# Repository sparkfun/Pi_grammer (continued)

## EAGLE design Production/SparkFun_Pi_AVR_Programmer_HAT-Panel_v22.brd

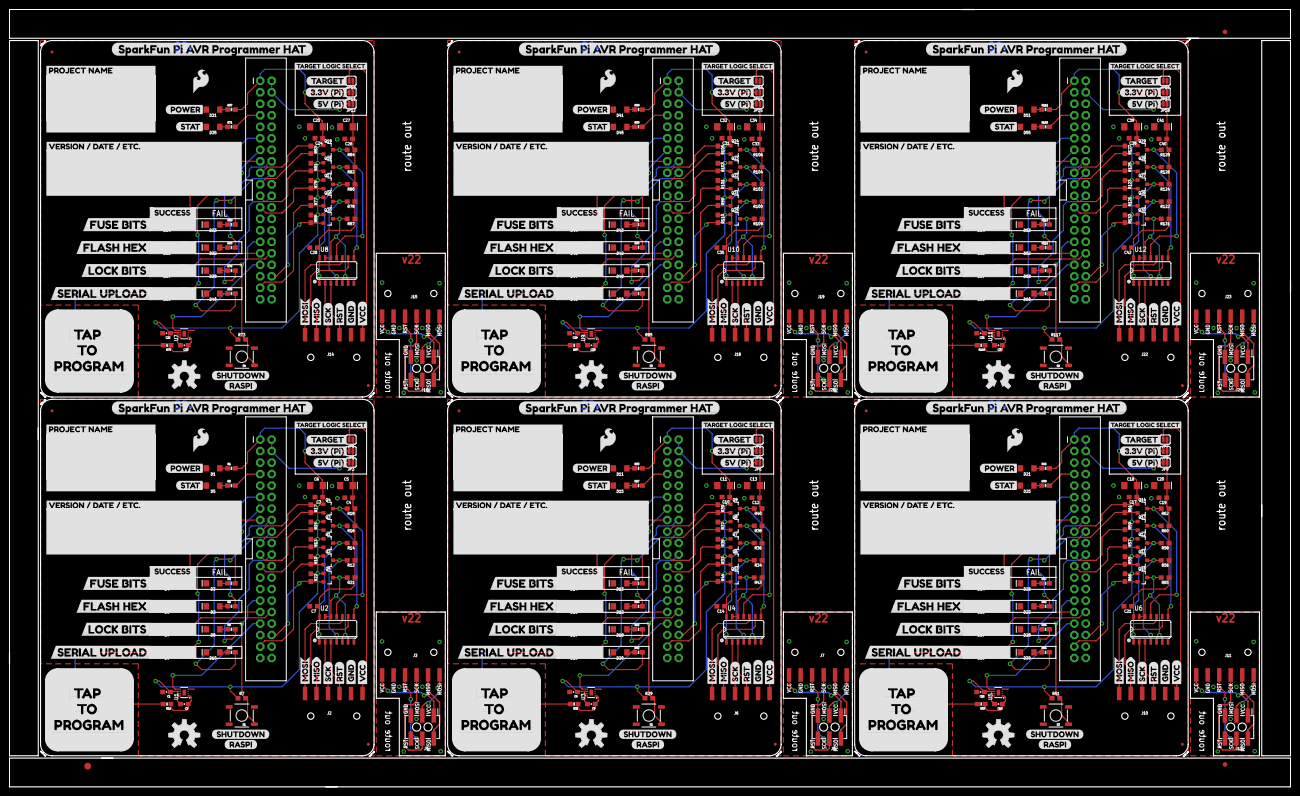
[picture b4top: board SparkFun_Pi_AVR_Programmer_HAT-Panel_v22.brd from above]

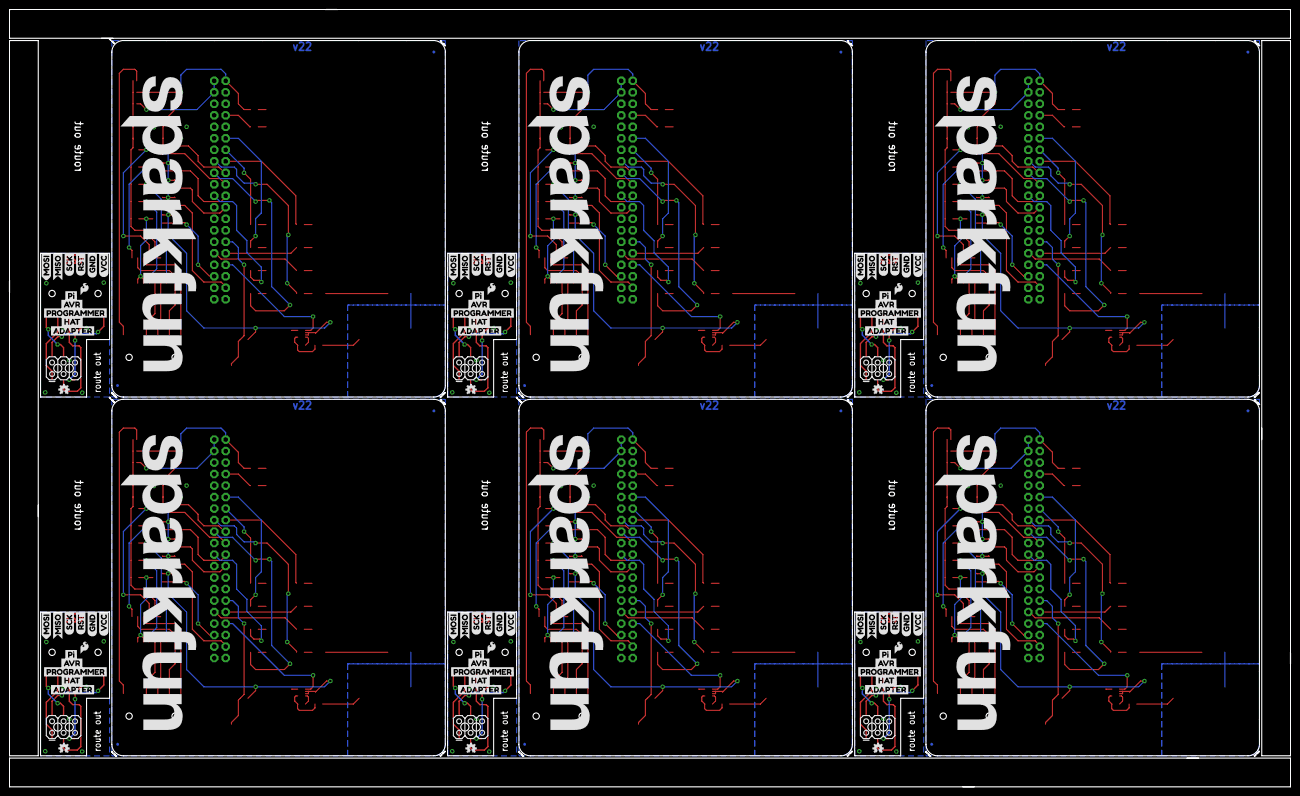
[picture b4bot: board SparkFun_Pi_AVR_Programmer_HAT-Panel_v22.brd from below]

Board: 2 copper layers, 283.0 x 171.7 mm, 597 parts (96 on the bottom side), 288 nets.

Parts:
C1, C8, C15, C22, C29, C36: 0.1uF; 0603-CAP
C2, C9, C16, C23, C30, C37: 10nF; 0603-CAP
C3, C4, C7, C10, C12, C14, C17, C19, C21, C24, C26, C28, C31, C33, C35, C38, C40, C42: 0.1uF; 0603
C5, C6, C11, C13, C18, C20, C25, C27, C32, C34, C39, C41: 10uF; EIA3216
D1, D4, D5, D6, D7, D9, D11, D14, D15, D16, D17, D19, D21, D24, D25, D26, D27, D29, D31, D34, D35, D36, D37, D39, D41, D44, D45, D46, D47, D49, D51, D54, D55, D56, D57, D59: GREEN; LED-1206
D2, D3, D8, D10, D12, D13, D18, D20, D22, D23, D28, D30, D32, D33, D38, D40, D42, D43, D48, D50, D52, D53, D58, D60: RED; LED-1206
E$1: FIDUCIAL-1.5X3
E$5, E$6: FIDUCIAL-1X2
FD1, FD2, FD3, FD4, FD5, FD6, FD7, FD8, FD9, FD10, FD11, FD12, FD13, FD14, FD15, FD16, FD17, FD18, FD19, FD20, FD21, FD22, FD23, FD24: FIDUCIALUFIDUCIAL; FIDUCIAL-MICRO
J1, J5, J9, J13, J17, J21: RASPBERRYPI-B+-GPIO; 2X20-SHROUDED
J2, J6, J10, J14, J18, J22: SPI; 1X06-SMD_RA_MALE
J3, J7, J11, J15, J19, J23: CABLE; 1X06-SMD_RA_MALE
J4, J8, J12, J16, J20, J24: AVR 3X2 TARGET; 2X3_SMT_POSTS
JP1, JP3, JP4, JP6, JP8, JP9, JP11, JP12, JP14, JP15, JP17, JP18: SMT-JUMPER_2_NO_SILK
JP2, JP5, JP7, JP10, JP13, JP16: SMT-JUMPER_2_NC_PASTE_SILK
LOGO1, LOGO7, LOGO12, LOGO17, LOGO22, LOGO27: SFE_LOGO_FLAME.2_INCH; SFE_LOGO_FLAME_.2
LOGO2, LOGO6, LOGO11, LOGO16, LOGO21, LOGO26: OSHW-LOGOL; OSHW-LOGO-L
LOGO3, LOGO8, LOGO13, LOGO18, LOGO23, LOGO28: SFE_LOGO_NAME.6_INCH; SFE_LOGO_NAME_.6
LOGO4, LOGO9, LOGO14, LOGO19, LOGO24, LOGO29: SFE_LOGO_FLAME.1_INCH; SFE_LOGO_FLAME_.1
LOGO5, LOGO10, LOGO15, LOGO20, LOGO25, LOGO30: OSHW-LOGOMINI; OSHW-LOGO-MINI
Q1, Q2, Q3, Q4, Q5, Q6, Q7, Q8, Q9, Q10, Q11, Q12, Q13, Q14, Q15, Q16, Q17, Q18, Q19, Q20, Q21, Q22, Q23, Q24, Q25, Q26, Q27, Q28, Q29, Q30: 220mA/50V/3.5Ω; SOT23-3
R1, R2, R3, R4, R5, R6, R8, R9, R19, R20, R23, R24, R25, R26, R27, R28, R30, R32, R41, R42, R45, R46, R47, R48, R49, R50, R52, R54, R63, R64, R67, R68, R69, R70, R71, R72, R74, R76, R85, R86, R89, R90, R91, R92, R93, R94, R96, R98, R107, R108, R111, R112, R113, R114, R115, R116, R118, R120, R129, R130: 1K; 0603-RES
R7, R29, R51, R73, R95, R117: 1k; 0603
R10, R12, R13, R14, R15, R16, R17, R18, R21, R22, R33, R34, R35, R36, R37, R38, R39, R40, R43, R44, R55, R56, R57, R58, R59, R60, R61, R62, R65, R66, R77, R78, R79, R80, R81, R82, R83, R84, R87, R88, R99, R100, R101, R102, R103, R104, R105, R106, R109, R110, R121, R122, R123, R124, R125, R126, R127, R128, R131, R132: 10k; 0603
R11, R31, R53, R75, R97, R119: 10k; 0603-RES
S1, S2, S3, S4, S5, S6: TACTILE-SWITCH-SMD
U1, U3, U5, U7, U9, U11: AT42QT1010 - UDFN; UDFN/USON_8_PAD
U2, U4, U6, U8, U10, U12: 74LVC4066; SO14
U$1, U$37, U$73, U$109, U$145, U$181: SPARKFUN_PI_AVR_PROGRAMMER_HAT0
U$2, U$38, U$74, U$110, U$146, U$182: PROJECT_NAME0
U$3, U$39, U$75, U$111, U$147, U$183: VERSION_#_DATE_#_ETC#0
U$4, U$40, U$76, U$112, U$148, U$184: TARGET_LOGIC_SELECT4
U$5, U$41, U$77, U$113, U$149, U$185: POWER0
U$6, U$42, U$78, U$114, U$150, U$186: STAT1
U$7, U$43, U$79, U$115, U$151, U$187: SHUTDOWN2
U$8, U$44, U$80, U$116, U$152, U$188: RASPI3
U$9, U$45, U$81, U$117, U$153, U$189: 3#3V_#PI#7
U$10, U$46, U$82, U$118, U$154, U$190: 5V_#PI#8
U$11, U$47, U$83, U$119, U$155, U$191: TARGET0
U$12, U$48, U$84, U$120, U$156, U$192: MISO1
U$13, U$49, U$85, U$121, U$157, U$193: MOSI0
U$14, U$50, U$86, U$122, U$158, U$194: SCK2
U$15, U$51, U$87, U$123, U$159, U$195: RST3
U$16, U$52, U$88, U$124, U$160, U$196: GND4
U$17, U$62, U$98, U$134, U$170, U$206: GND1
U$18, U$53, U$89, U$125, U$161, U$197: TAP0
U$19, U$54, U$90, U$126, U$162, U$198: TO1
U$20, U$55, U$91, U$127, U$163, U$199: PROGRAM2
U$21, U$31, U$61, U$67, U$97, U$103, U$133, U$139, U$169, U$175, U$205, U$211: VCC0
U$22, U$56, U$92, U$128, U$164, U$200: SUCCESS0
U$23, U$57, U$93, U$129, U$165, U$201: FUSE_BITS2
U$24, U$58, U$94, U$130, U$166, U$202: FLASH_HEX3
U$25, U$59, U$95, U$131, U$167, U$203: LOCK_BITS4
U$26, U$60, U$96, U$132, U$168, U$204: SERIAL_UPLOAD5
U$27, U$63, U$99, U$135, U$171, U$207: MISO5
U$28, U$64, U$100, U$136, U$172, U$208: MOSI4
U$29, U$65, U$101, U$137, U$173, U$209: RST2
U$30, U$66, U$102, U$138, U$174, U$210: SCK3
U$32, U$68, U$104, U$140, U$176, U$212: PI0
U$33, U$69, U$105, U$141, U$177, U$213: AVR1
U$34, U$70, U$106, U$142, U$178, U$214: PROGRAMMER2
U$35, U$71, U$107, U$143, U$179, U$215: HAT3
U$36, U$72, U$108, U$144, U$180, U$216: ADAPTER4

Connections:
3.3V: C1.1, C3.1, C6.+, J1.1, J1.17, JP1.2, Q1.1, Q2.1, Q3.1, Q4.1, Q5.1, R1.2, R7.1, R10.1, R13.1, R15.1, R17.1, R22.1, U1.6, U1.7
3.3V1: C8.1, C10.1, C11.+, J5.1, J5.17, JP4.2, Q6.1, Q7.1, Q8.1, Q9.1, Q10.1, R23.2, R29.1, R33.1, R35.1, R37.1, R39.1, R44.1, U3.6, U3.7
3.3V2: C15.1, C17.1, C18.+, J9.1, J9.17, JP8.2, Q11.1, Q12.1, Q13.1, Q14.1, Q15.1, R45.2, R51.1, R55.1, R57.1, R59.1, R61.1, R66.1, U5.6, U5.7
3.3V3: C22.1, C24.1, C25.+, J13.1, J13.17, JP11.2, Q16.1, Q17.1, Q18.1, Q19.1, Q20.1, R67.2, R73.1, R77.1, R79.1, R81.1, R83.1, R88.1, U7.6, U7.7
3.3V4: C29.1, C31.1, C32.+, J17.1, J17.17, JP14.2, Q21.1, Q22.1, Q23.1, Q24.1, Q25.1, R89.2, R95.1, R99.1, R101.1, R103.1, R105.1, R110.1, U9.6, U9.7
3.3V5: C36.1, C38.1, C39.+, J21.1, J21.17, JP17.2, Q26.1, Q27.1, Q28.1, Q29.1, Q30.1, R111.2, R117.1, R121.1, R123.1, R125.1, R127.1, R132.1, U11.6, U11.7
5V: J1.2, J1.4, JP3.2
5V1: J5.2, J5.4, JP6.2
5V2: J9.2, J9.4, JP9.2
5V3: J13.2, J13.4, JP12.2
5V4: J17.2, J17.4, JP15.2
5V5: J21.2, J21.4, JP18.2
BRD_MISO: J2.2, U2.9
BRD_MISO1: J6.2, U4.9
BRD_MISO2: J10.2, U6.9
BRD_MISO3: J14.2, U8.9
BRD_MISO4: J18.2, U10.9
BRD_MISO5: J22.2, U12.9
BRD_MOSI: J2.1, U2.10
BRD_MOSI1: J6.1, U4.10
BRD_MOSI2: J10.1, U6.10
BRD_MOSI3: J14.1, U8.10
BRD_MOSI4: J18.1, U10.10
BRD_MOSI5: J22.1, U12.10
BRD_RST: J2.4, U2.3
BRD_RST1: J6.4, U4.3
BRD_RST2: J10.4, U6.3
BRD_RST3: J14.4, U8.3
BRD_RST4: J18.4, U10.3
BRD_RST5: J22.4, U12.3
BRD_SCK: J2.3, U2.2
BRD_SCK1: J6.3, U4.2
BRD_SCK2: J10.3, U6.2
BRD_SCK3: J14.3, U8.2
BRD_SCK4: J18.3, U10.2
BRD_SCK5: J22.3, U12.2
CAPSENSE: J1.33, U1.5
CAPSENSE1: J5.33, U3.5
CAPSENSE2: J9.33, U5.5
CAPSENSE3: J13.33, U7.5
CAPSENSE4: J17.33, U9.5
CAPSENSE5: J21.33, U11.5
FLASH_HEX_FAIL: J1.11, R2.2
FLASH_HEX_FAIL1: J5.11, R24.2
FLASH_HEX_FAIL2: J9.11, R46.2
FLASH_HEX_FAIL3: J13.11, R68.2
FLASH_HEX_FAIL4: J17.11, R90.2
FLASH_HEX_FAIL5: J21.11, R112.2
FLASH_HEX_PASS: J1.31, R6.2
FLASH_HEX_PASS1: J5.31, R28.2
FLASH_HEX_PASS2: J9.31, R50.2
FLASH_HEX_PASS3: J13.31, R72.2
FLASH_HEX_PASS4: J17.31, R94.2
FLASH_HEX_PASS5: J21.31, R116.2
FUSE_BITS_FAIL: J1.13, R3.2
FUSE_BITS_FAIL1: J5.13, R25.2
FUSE_BITS_FAIL2: J9.13, R47.2
FUSE_BITS_FAIL3: J13.13, R69.2
FUSE_BITS_FAIL4: J17.13, R91.2
FUSE_BITS_FAIL5: J21.13, R113.2
FUSE_BITS_PASS: J1.15, R4.2
FUSE_BITS_PASS1: J5.15, R26.2
FUSE_BITS_PASS2: J9.15, R48.2
FUSE_BITS_PASS3: J13.15, R70.2
FUSE_BITS_PASS4: J17.15, R92.2
FUSE_BITS_PASS5: J21.15, R114.2
GND: C1.2, C3.2, C4.2, C5.-, C6.-, C7.2, D1.C, D2.C, D3.C, D4.C, D5.C, D6.C, D7.C, D8.C, D9.C, D10.C, J1.6, J1.9, J1.14, J1.20, J1.25, J1.30, J1.34, J1.39, J2.5, S1.3, U1.4, U2.7
GND1: C8.2, C10.2, C11.-, C12.2, C13.-, C14.2, D11.C, D12.C, D13.C, D14.C, D15.C, D16.C, D17.C, D18.C, D19.C, D20.C, J5.6, J5.9, J5.14, J5.20, J5.25, J5.30, J5.34, J5.39, J6.5, S2.3, U3.4, U4.7
GND2: C15.2, C17.2, C18.-, C19.2, C20.-, C21.2, D21.C, D22.C, D23.C, D24.C, D25.C, D26.C, D27.C, D28.C, D29.C, D30.C, J9.6, J9.9, J9.14, J9.20, J9.25, J9.30, J9.34, J9.39, J10.5, S3.3, U5.4, U6.7
GND3: C22.2, C24.2, C25.-, C26.2, C27.-, C28.2, D31.C, D32.C, D33.C, D34.C, D35.C, D36.C, D37.C, D38.C, D39.C, D40.C, J13.6, J13.9, J13.14, J13.20, J13.25, J13.30, J13.34, J13.39, J14.5, S4.3, U7.4, U8.7
GND4: C29.2, C31.2, C32.-, C33.2, C34.-, C35.2, D41.C, D42.C, D43.C, D44.C, D45.C, D46.C, D47.C, D48.C, D49.C, D50.C, J17.6, J17.9, J17.14, J17.20, J17.25, J17.30, J17.34, J17.39, J18.5, S5.3, U9.4, U10.7
GND5: C36.2, C38.2, C39.-, C40.2, C41.-, C42.2, D51.C, D52.C, D53.C, D54.C, D55.C, D56.C, D57.C, D58.C, D59.C, D60.C, J21.6, J21.9, J21.14, J21.20, J21.25, J21.30, J21.34, J21.39, J22.5, S6.3, U11.4, U12.7
GND_C: J3.5, J4.5
GND_C1: J7.5, J8.5
GND_C2: J11.5, J12.5
GND_C3: J15.5, J16.5
GND_C4: J19.5, J20.5
GND_C5: J23.5, J24.5
LOCK_BITS_FAIL: J1.22, R9.2
LOCK_BITS_FAIL1: J5.22, R32.2
LOCK_BITS_FAIL2: J9.22, R54.2
LOCK_BITS_FAIL3: J13.22, R76.2
LOCK_BITS_FAIL4: J17.22, R98.2
LOCK_BITS_FAIL5: J21.22, R120.2
LOCK_BITS_PASS: J1.32, R8.2
LOCK_BITS_PASS1: J5.32, R30.2
LOCK_BITS_PASS2: J9.32, R52.2
LOCK_BITS_PASS3: J13.32, R74.2
LOCK_BITS_PASS4: J17.32, R96.2
LOCK_BITS_PASS5: J21.32, R118.2
MISO: J1.21, Q3.2, R15.2
MISO1: J5.21, Q8.2, R37.2
MISO2: J9.21, Q13.2, R59.2
MISO3: J13.21, Q18.2, R81.2
MISO4: J17.21, Q23.2, R103.2
MISO5: J21.21, Q28.2, R125.2
MISO_C: J3.2, J4.2
MISO_C1: J7.2, J8.2
MISO_C2: J11.2, J12.2
MISO_C3: J15.2, J16.2
MISO_C4: J19.2, J20.2
MISO_C5: J23.2, J24.2
MISO_T: Q3.3, R16.2, U2.8
MISO_T1: Q8.3, R38.2, U4.8
MISO_T2: Q13.3, R60.2, U6.8
MISO_T3: Q18.3, R82.2, U8.8
MISO_T4: Q23.3, R104.2, U10.8
MISO_T5: Q28.3, R126.2, U12.8
MOSI: J1.19, Q4.2, R17.2
MOSI1: J5.19, Q9.2, R39.2
MOSI2: J9.19, Q14.2, R61.2
MOSI3: J13.19, Q19.2, R83.2
MOSI4: J17.19, Q24.2, R105.2
MOSI5: J21.19, Q29.2, R127.2
MOSI_C: J3.1, J4.3
MOSI_C1: J7.1, J8.3
MOSI_C2: J11.1, J12.3
MOSI_C3: J15.1, J16.3
MOSI_C4: J19.1, J20.3
MOSI_C5: J23.1, J24.3
MOSI_T: Q4.3, R18.2, U2.11
MOSI_T1: Q9.3, R40.2, U4.11
MOSI_T2: Q14.3, R62.2, U6.11
MOSI_T3: Q19.3, R84.2, U8.11
MOSI_T4: Q24.3, R106.2, U10.11
MOSI_T5: Q29.3, R128.2, U12.11
unnamed: D6.A, R6.1
unnamed: D1.A, R1.1
unnamed: D2.A, R2.1
unnamed: D3.A, R3.1
unnamed: D7.A, R8.1
unnamed: D4.A, R4.1
unnamed: D5.A, R5.1
unnamed: D8.A, R9.1
unnamed: D11.A, R23.1
unnamed: C2.2, U1.8
unnamed: C2.1, R11.1, U1.1
unnamed: D12.A, R24.1
unnamed: D9.A, R19.1
unnamed: D10.A, R20.1
unnamed: D13.A, R25.1
unnamed: D14.A, R26.1
unnamed: D15.A, R27.1
unnamed: D16.A, R28.1
unnamed: D17.A, R30.1
unnamed: C9.2, U3.8
unnamed: C9.1, R31.1, U3.1
unnamed: D18.A, R32.1
unnamed: D19.A, R41.1
unnamed: D20.A, R42.1
unnamed: D21.A, R45.1
unnamed: D22.A, R46.1
unnamed: D23.A, R47.1
unnamed: D24.A, R48.1
unnamed: D25.A, R49.1
unnamed: D26.A, R50.1
unnamed: D27.A, R52.1
unnamed: C16.2, U5.8
unnamed: C16.1, R53.1, U5.1
unnamed: D28.A, R54.1
unnamed: D29.A, R63.1
unnamed: D30.A, R64.1
unnamed: D31.A, R67.1
unnamed: D32.A, R68.1
unnamed: D33.A, R69.1
unnamed: D34.A, R70.1
unnamed: D35.A, R71.1
unnamed: D36.A, R72.1
unnamed: D37.A, R74.1
unnamed: C23.2, U7.8
unnamed: C23.1, R75.1, U7.1
unnamed: D38.A, R76.1
unnamed: D39.A, R85.1
unnamed: D40.A, R86.1
unnamed: D41.A, R89.1
unnamed: D42.A, R90.1
unnamed: D43.A, R91.1
unnamed: D44.A, R92.1
unnamed: D45.A, R93.1
unnamed: D46.A, R94.1
unnamed: D47.A, R96.1
unnamed: C30.2, U9.8
unnamed: C30.1, R97.1, U9.1
unnamed: D48.A, R98.1
unnamed: D49.A, R107.1
unnamed: D50.A, R108.1
unnamed: D51.A, R111.1
unnamed: D52.A, R112.1
unnamed: D53.A, R113.1
unnamed: D54.A, R114.1
unnamed: D55.A, R115.1
unnamed: D56.A, R116.1
unnamed: D57.A, R118.1
unnamed: C37.2, U11.8
unnamed: C37.1, R119.1, U11.1
unnamed: D58.A, R120.1
unnamed: D59.A, R129.1
unnamed: D60.A, R130.1
PGM_CTRL: J1.36, Q5.2, R22.2
PGM_CTRL1: J5.36, Q10.2, R44.2
PGM_CTRL2: J9.36, Q15.2, R66.2
PGM_CTRL3: J13.36, Q20.2, R88.2
PGM_CTRL4: J17.36, Q25.2, R110.2
PGM_CTRL5: J21.36, Q30.2, R132.2
PGM_CTRL_T: Q5.3, R21.2, U2.5, U2.6, U2.12, U2.13
PGM_CTRL_T1: Q10.3, R43.2, U4.5, U4.6, U4.12, U4.13
PGM_CTRL_T2: Q15.3, R65.2, U6.5, U6.6, U6.12, U6.13
PGM_CTRL_T3: Q20.3, R87.2, U8.5, U8.6, U8.12, U8.13
PGM_CTRL_T4: Q25.3, R109.2, U10.5, U10.6, U10.12, U10.13
PGM_CTRL_T5: Q30.3, R131.2, U12.5, U12.6, U12.12, U12.13
RST: J1.37, Q2.2, R10.2
RST1: J5.37, Q6.2, R33.2
RST2: J9.37, Q11.2, R55.2
RST3: J13.37, Q16.2, R77.2
RST4: J17.37, Q21.2, R99.2
RST5: J21.37, Q26.2, R121.2
RST_C: J3.4, J4.6
RST_C1: J7.4, J8.6
RST_C2: J11.4, J12.6
RST_C3: J15.4, J16.6
RST_C4: J19.4, J20.6
RST_C5: J23.4, J24.6
RST_T: Q2.3, R12.2, U2.4
RST_T1: Q6.3, R34.2, U4.4
RST_T2: Q11.3, R56.2, U6.4
RST_T3: Q16.3, R78.2, U8.4
RST_T4: Q21.3, R100.2, U10.4
RST_T5: Q26.3, R122.2, U12.4
SCK: J1.23, Q1.2, R13.2
SCK1: J5.23, Q7.2, R35.2
SCK2: J9.23, Q12.2, R57.2
SCK3: J13.23, Q17.2, R79.2
SCK4: J17.23, Q22.2, R101.2
SCK5: J21.23, Q27.2, R123.2
SCK_C: J3.3, J4.4
SCK_C1: J7.3, J8.4
SCK_C2: J11.3, J12.4
SCK_C3: J15.3, J16.4
SCK_C4: J19.3, J20.4
SCK_C5: J23.3, J24.4
SCK_T: Q1.3, R14.2, U2.1
SCK_T1: Q7.3, R36.2, U4.1
SCK_T2: Q12.3, R58.2, U6.1
SCK_T3: Q17.3, R80.2, U8.1
SCK_T4: Q22.3, R102.2, U10.1
SCK_T5: Q27.3, R124.2, U12.1
SCRIPT: J1.7, R5.2
SCRIPT1: J5.7, R27.2
SCRIPT2: J9.7, R49.2
SCRIPT3: J13.7, R71.2
SCRIPT4: J17.7, R93.2
SCRIPT5: J21.7, R115.2
SERIAL_UPLOAD_FAIL: J1.18, R20.2
SERIAL_UPLOAD_FAIL1: J5.18, R42.2
SERIAL_UPLOAD_FAIL2: J9.18, R64.2
SERIAL_UPLOAD_FAIL3: J13.18, R86.2
SERIAL_UPLOAD_FAIL4: J17.18, R108.2
SERIAL_UPLOAD_FAIL5: J21.18, R130.2
SERIAL_UPLOAD_PASS: J1.16, R19.2
SERIAL_UPLOAD_PASS1: J5.16, R41.2
SERIAL_UPLOAD_PASS2: J9.16, R63.2
SERIAL_UPLOAD_PASS3: J13.16, R85.2
SERIAL_UPLOAD_PASS4: J17.16, R107.2
SERIAL_UPLOAD_PASS5: J21.16, R129.2
SHUTDOWN: J1.29, R7.2, S1.1
SHUTDOWN1: J5.29, R29.2, S2.1
SHUTDOWN2: J9.29, R51.2, S3.1
SHUTDOWN3: J13.29, R73.2, S4.1
SHUTDOWN4: J17.29, R95.2, S5.1
SHUTDOWN5: J21.29, R117.2, S6.1
VCC_C: J3.6, J4.1
VCC_C1: J7.6, J8.1
VCC_C2: J11.6, J12.1
VCC_C3: J15.6, J16.1
VCC_C4: J19.6, J20.1
VCC_C5: J23.6, J24.1
VCC_T: J2.6, JP5.2
VCC_T1: J6.6, JP2.2
VCC_T2: J10.6, JP7.2
VCC_T3: J14.6, JP10.2
VCC_T4: J18.6, JP13.2
VCC_T5: J22.6, JP16.2
VCC_T_SELECTED: C4.1, C5.+, C7.1, JP1.1, JP3.1, JP5.1, R12.1, R14.1, R16.1, R18.1, R21.1, U2.14
VCC_T_SELECTED1: C12.1, C13.+, C14.1, JP2.1, JP4.1, JP6.1, R34.1, R36.1, R38.1, R40.1, R43.1, U4.14
VCC_T_SELECTED2: C19.1, C20.+, C21.1, JP7.1, JP8.1, JP9.1, R56.1, R58.1, R60.1, R62.1, R65.1, U6.14
VCC_T_SELECTED3: C26.1, C27.+, C28.1, JP10.1, JP11.1, JP12.1, R78.1, R80.1, R82.1, R84.1, R87.1, U8.14
VCC_T_SELECTED4: C33.1, C34.+, C35.1, JP13.1, JP14.1, JP15.1, R100.1, R102.1, R104.1, R106.1, R109.1, U10.14
VCC_T_SELECTED5: C40.1, C41.+, C42.1, JP16.1, JP17.1, JP18.1, R122.1, R124.1, R126.1, R128.1, R131.1, U12.14
